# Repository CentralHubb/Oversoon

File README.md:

# Oversoon
Custom PCB design for geolocation sensing, wifi communications, and LED display

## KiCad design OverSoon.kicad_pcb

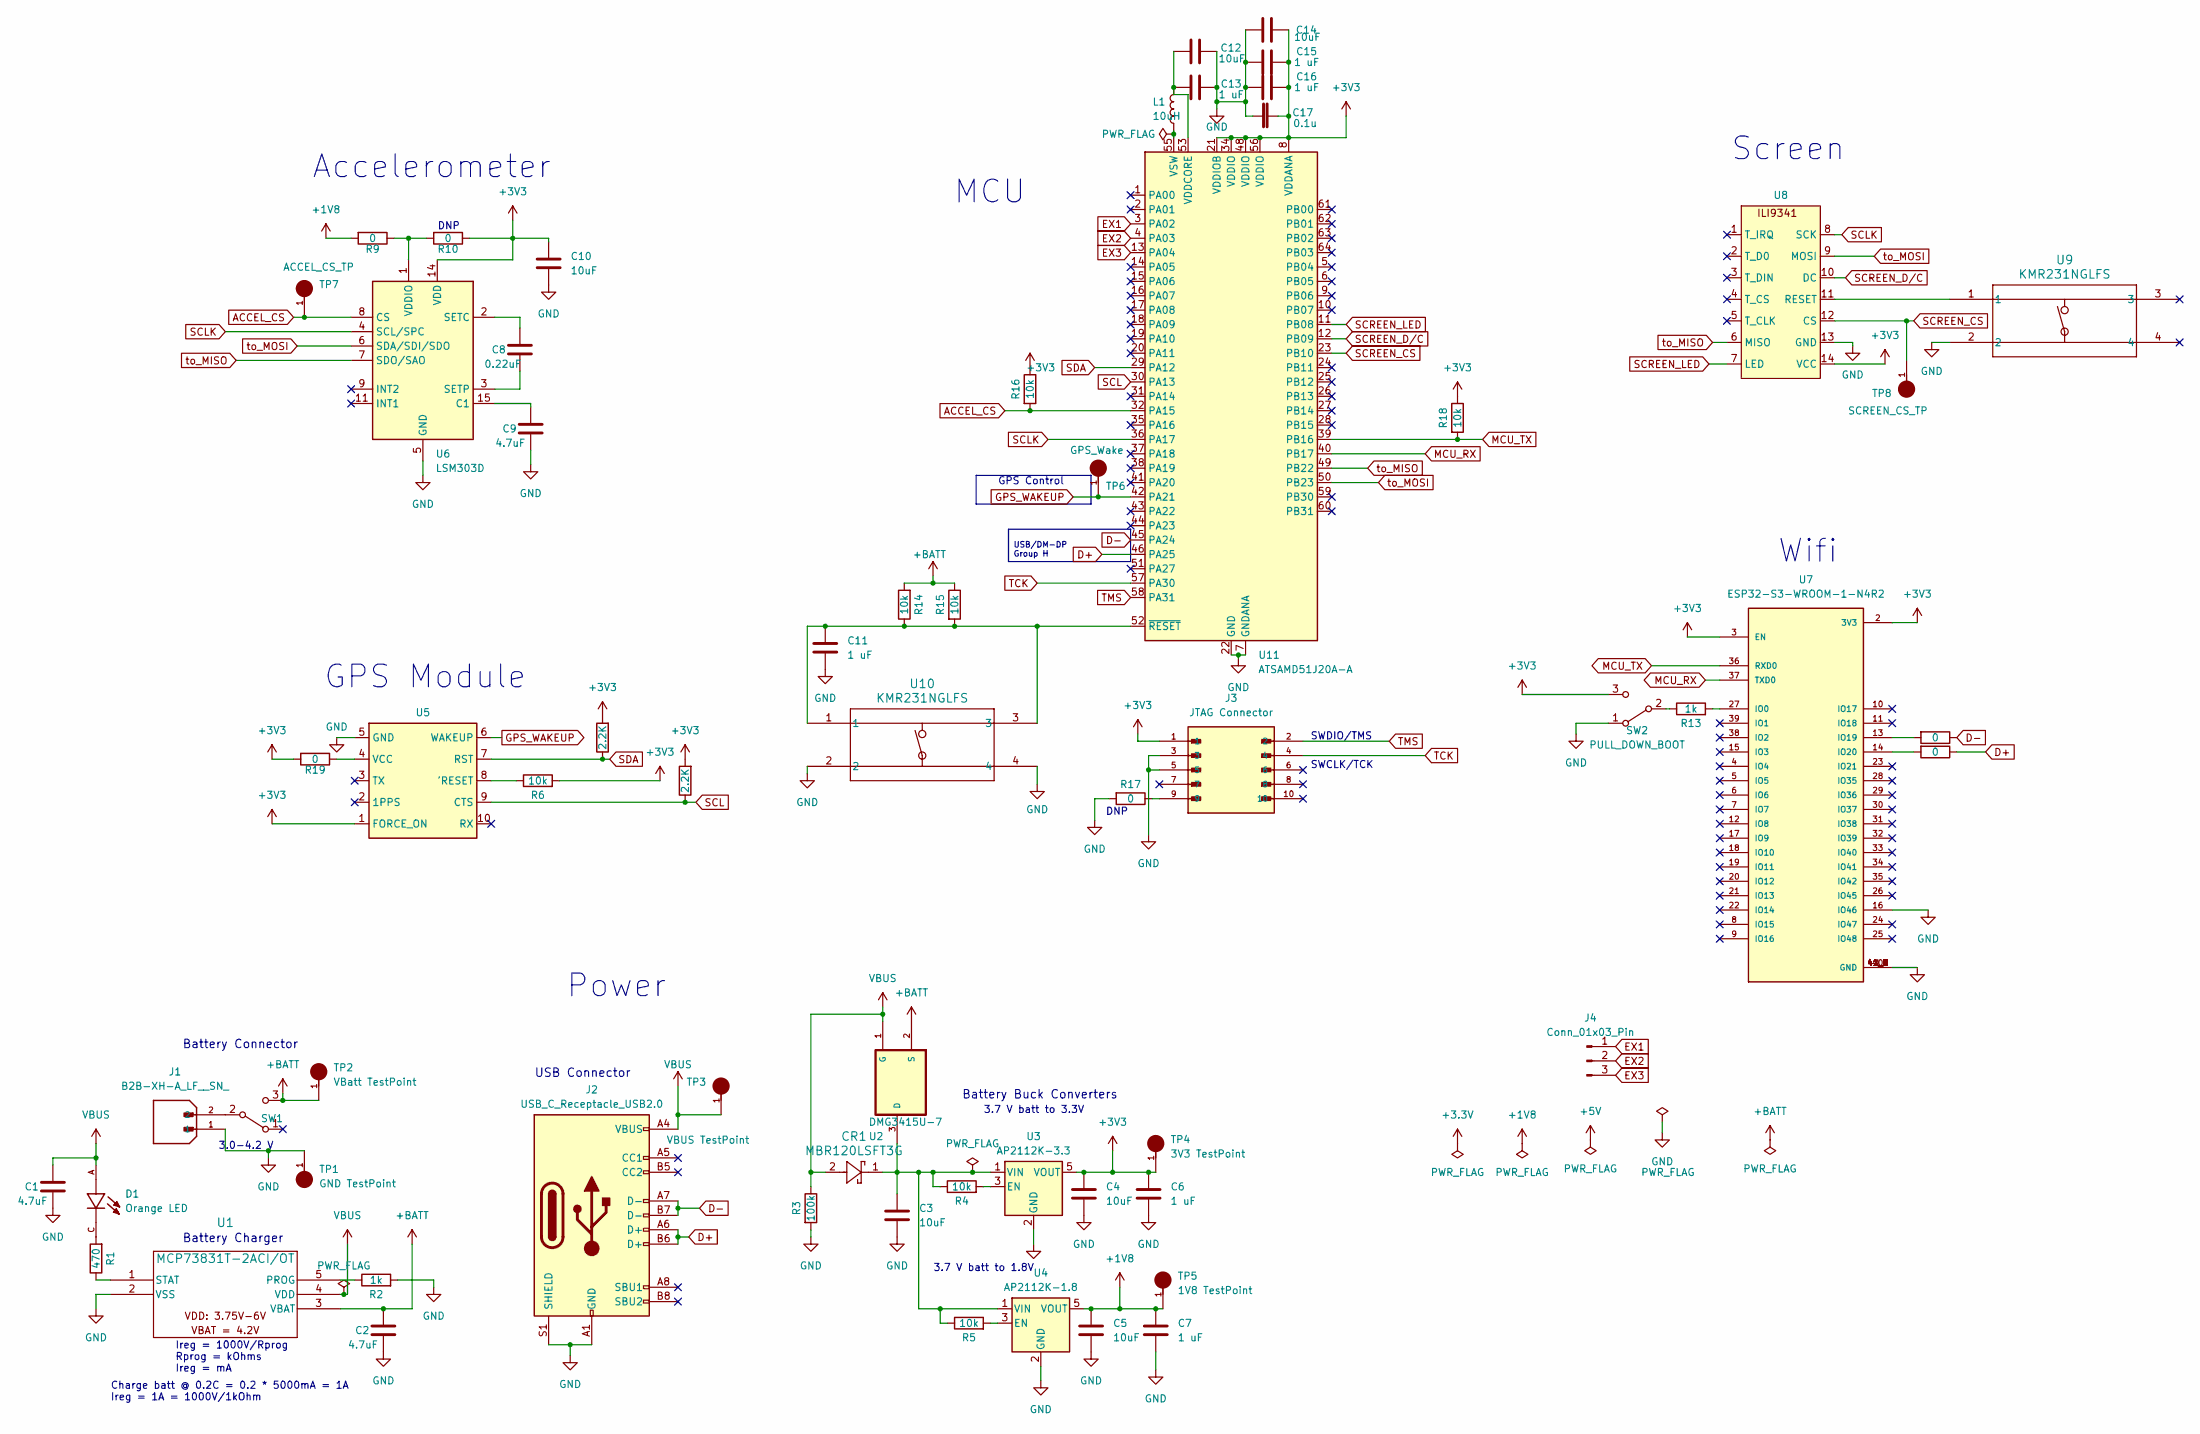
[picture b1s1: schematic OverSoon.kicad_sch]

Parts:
C1, C2, C9: 4.7uF; C_0805_2012Metric_Pad1.18x1.45mm_HandSolder; Mfr P/N GRM21BR71C475KE51L
C3, C4, C5, C10, C12, C14: 10uF; C_0805_2012Metric_Pad1.18x1.45mm_HandSolder; Mfr P/N CC0805JRNPO9BN100
C6, C7, C11, C13, C15, C16: 1 uF; C_0805_2012Metric_Pad1.18x1.45mm_HandSolder; Mfr P/N CL21F105ZBFNNNE
C8: 0.22uF; C_0805_2012Metric_Pad1.18x1.45mm_HandSolder; Mfr P/N GCM21BR71H224KA37L
C17: 0.1u; C_0805_2012Metric_Pad1.18x1.45mm_HandSolder; Mfr P/N 08056D104KAT2A
CR1: MBR120LSFT3G; SDO_SOD-123FL498_OSI; Mfr P/N MBR120LSFT3G
D1: Orange LED; LEDC1608X55N; Mfr P/N LTST-C191KFKT
J1: B2B-XH-A_LF__SN_; JST_B2B-XH-A_LF__SN_; PARTREV N/A
J2: USB_C_Receptacle_USB2.0; USB_C_Receptacle_XKB_U262-16XN-4BVC11; Mfr P/N U262-161N-4BVC11
J3: JTAG Connector; CNC_3221-10-0300-00; Mfr P/N 3221-10-0300-00
J4: Conn_01x03_Pin; PinHeader_1x03_P2.54mm_Vertical; Mfr P/N M20-9990345
L1: 10uH; L_0805_2012Metric_Pad1.15x1.40mm_HandSolder; Mfr P/N LBR2012T100K
R1: 470; R_0805_2012Metric_Pad1.20x1.40mm_HandSolder; Mfr P/N RMCF0805JT470R
R2, R13: 1k; R_0805_2012Metric_Pad1.20x1.40mm_HandSolder; Mfr P/N RMCF0805FT1K00
R3: 100k; R_0805_2012Metric_Pad1.20x1.40mm_HandSolder; Mfr P/N RMCF0805FT100K
R4, R5, R6, R14, R15, R16, R18: 10k; R_0805_2012Metric_Pad1.20x1.40mm_HandSolder; Mfr P/N RMCF0805JT10K0
R7, R8: 2.2K; R_0805_2012Metric_Pad1.20x1.40mm_HandSolder; Mfr P/N RT0805BRD072K23L
R9, R10, R11, R12, R17, R19: 0; R_0805_2012Metric_Pad1.20x1.40mm_HandSolder; Mfr P/N CRCW08050000Z0EAHP
SW1, SW2: PULL_DOWN_BOOT; SW_JS102011SAQN; Mfr P/N JS102011SAQN
TP1: GND TestPoint; HARWIN_S2751-46R; Mfr P/N S2751-46R
TP2: VBatt TestPoint; HARWIN_S2751-46R; Mfr P/N S2751-46R
TP3: VBUS TestPoint; HARWIN_S2751-46R; Mfr P/N S2751-46R
TP4: 3V3 TestPoint; HARWIN_S2751-46R; Mfr P/N S2751-46R
TP5: 1V8 TestPoint; HARWIN_S2751-46R; Mfr P/N S2751-46R
TP6: GPS_Wake; HARWIN_S2751-46R; Mfr P/N S2751-46R
TP7: ACCEL_CS_TP; HARWIN_S2751-46R; Mfr P/N S2751-46R
TP8: SCREEN_CS_TP; HARWIN_S2751-46R; Mfr P/N S2751-46R
U1: MCP73831T-2ACI/OT; SOT-23-5_MC_MCH; Mfr P/N MCP73831T-2ACI/OT
U2: DMG3415U-7; SOT95P240X105-3N; Mfr P/N DMG3415U-7
U3: AP2112K-3.3; SOT-23-5; Mfr P/N AP2112K-3.3TRG1
U4: AP2112K-1.8; SOT-23-5; Mfr P/N AP2112K-1.8TRG1
U5: ORG1510-R02
U6: LSM303D; LGA-16_3x3mm_P0.5mm; Mfr P/N LSM303D
U7: ESP32-S3-WROOM-1-N4R2; XCVR_ESP32-S3-WROOM-1-N4R2; Mfr P/N ESP32-S3-WROOM-1-N4R2
U8: ILI9341; Mfr P/N 6-104910-3
U9, U10: KMR231NGLFS; IC4_KMR231NGLFS_CNK; Mfr P/N KMR231NG LFS
U11: ATSAMD51J20A-A; TQFP-64_10x10mm_P0.5mm; Mfr P/N ATSAMD51J20A-AU

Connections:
+1V8: C5.1, C7.1, R9.2, TP5.1, U4.5 (VOUT)
+3V3: C4.1, C6.1, C10.1, C14.2, C15.2, C16.2, C17.2, J3.1, R6.2, R7.2, R8.2, R10.1, R16.1, R18.1, R19.2, SW2.3 (C), TP4.1, U3.5 (VOUT), U5.1 (FORCE_ON), U6.14 (VDD), U7.2 (3V3), U7.3 (EN), U8.14 (VCC), U11.8 (VDDANA), U11.21 (VDDIOB), U11.34 (VDDIO), U11.48 (VDDIO), U11.56 (VDDIO)
+BATT: C2.1, R14.2, R15.1, SW1.3 (C), TP2.1, U1.3 (VBAT), U2.2 (S)
ACCEL_CS: R16.2, TP7.1, U6.8 (CS), U11.32 (PA15)
D+: J2.A6 (D+), J2.B6 (D+), R12.1, U11.46 (PA25)
D-: J2.A7 (D-), J2.B7 (D-), R11.1, U11.45 (PA24)
EX1: J4.1, U11.3 (PA02)
EX2: J4.2, U11.4 (PA03)
EX3: J4.3, U11.13 (PA04)
GND: C1.2, C2.2, C3.2, C4.2, C5.2, C6.2, C7.2, C9.2, C10.2, C11.2, C12.2, C13.2, C14.1, C15.1, C16.1, C17.1, J1.1, J2.A1 (GND), J2.A12 (GND), J2.B1 (GND), J2.B12 (GND), J2.S1 (SHIELD), J3.3, J3.5, R2.2, R3.2, R17.2, SW2.1 (A), TP1.1, U1.2 (VSS), U3.2 (GND), U4.2 (GND), U5.5 (GND), U6.5 (GND), U6.10 (GND), U6.12 (GND), U6.13 (GND), U6.16 (GND), U7.1 (GND), U7.16 (IO46), U7.40 (GND), U7.41_1 (GND), U7.41_2 (GND), U7.41_3 (GND), U7.41_4 (GND), U7.41_5 (GND), U7.41_6 (GND), U7.41_7 (GND), U7.41_8 (GND), U7.41_9 (GND), U8.13 (GND), U9.2, U10.2, U10.4, U11.7 (GNDANA), U11.22 (GND), U11.33 (GND), U11.47 (GND), U11.54 (GND)
GPS_WAKEUP: TP6.1, U5.6 (WAKEUP), U11.42 (PA21)
MCU_RX: U7.37 (TXD0), U11.40 (PB17)
MCU_TX: R18.2, U7.36 (RXD0), U11.39 (PB16)
unnamed: D1.C, R1.2
unnamed: J3.9, R17.1
unnamed: J1.2, SW1.2 (B)
unnamed: R13.1, SW2.2 (B)
unnamed: R2.1, U1.5 (PROG)
unnamed: R1.1, U1.1 (STAT)
unnamed: C3.1, CR1.1, R4.1, R5.1, U2.3 (D), U3.1 (VIN), U4.1 (VIN)
unnamed: R4.2, U3.3 (EN)
unnamed: R5.2, U4.3 (EN)
unnamed: R6.1, U5.8 ('RESET)
unnamed: R19.1, U5.4 (VCC)
unnamed: C9.1, U6.15 (C1)
unnamed: C8.1, U6.2 (SETC)
unnamed: C8.2, U6.3 (SETP)
unnamed: R9.1, R10.2, U6.1 (VDDIO)
unnamed: R13.2, U7.27 (IO0)
unnamed: R11.2, U7.13 (IO19)
unnamed: R12.2, U7.14 (IO20)
unnamed: U8.11 (RESET), U9.1
unnamed: C12.1, C13.1, L1.2, U11.53 (VDDCORE)
unnamed: L1.1, U11.55 (VSW)
unnamed: C11.1, R14.1, R15.2, U10.1, U10.3, U11.52 (~RESET)
SCL: R8.1, U5.9 (CTS), U11.30 (PA13)
SCLK: U6.4 (SCL/SPC), U8.8 (SCK), U11.36 (PA17)
SCREEN_CS: TP8.1, U8.12 (CS), U11.23 (PB10)
SCREEN_D/C: U8.10 (DC), U11.12 (PB09)
SCREEN_LED: U8.7 (LED), U11.11 (PB08)
SDA: R7.1, U5.7 (RST), U11.29 (PA12)
TCK: J3.4, U11.57 (PA30)
TMS: J3.2, U11.58 (PA31)
VBUS: C1.1, CR1.2, D1.A, J2.A4 (VBUS), J2.A9 (VBUS), J2.B4 (VBUS), J2.B9 (VBUS), R3.1, TP3.1, U1.4 (VDD), U2.1 (G)
to_MISO: U6.7 (SDO/SAO), U8.6 (MISO), U11.49 (PB22)
to_MOSI: U6.6 (SDA/SDI/SDO), U8.9 (MOSI), U11.50 (PB23)

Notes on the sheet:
USB/DM-DP Group H
Wifi
GPS Control
Power
Accelerometer
DNP
SWCLK/TCK
3.7 V batt to 1.8V
3.0-4.2 V
Screen
USB Connector
Battery Charger
Ireg = 1000V/Rprog Rprog = kOhms Ireg = mA
Battery Buck Converters
Battery Connector
MCU
Charge batt @ 0.2C = 0.2 * 5000mA = 1A Ireg = 1A = 1000V/1kOhm
SWDIO/TMS
3.7 V batt to 3.3V
GPS Module

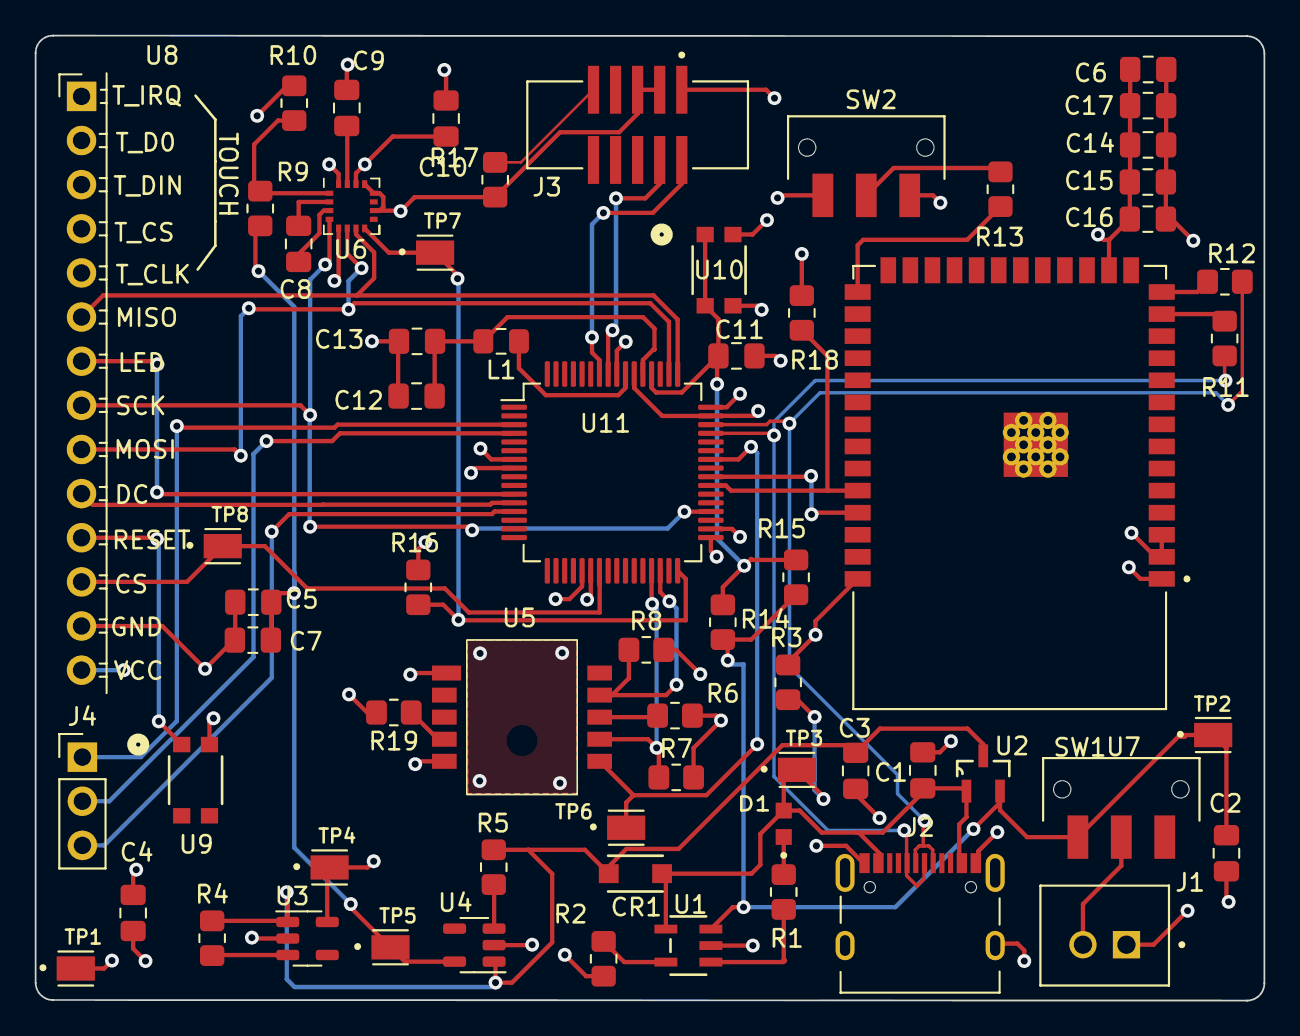
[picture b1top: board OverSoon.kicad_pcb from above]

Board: 4 copper layers, 70.7 x 55.5 mm, 64 parts (0 on the bottom side), 46 nets.

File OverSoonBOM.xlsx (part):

Source: | C:\Users\theol\OneDrive\Documents\KiCad\7.0\projects\OverSoon\OverSoon.kicad_sch
Date: | 45556
Tool: | Eeschema 7.0.8
Generator: | D:\Program Files\KiCad\7.0\bin\scripting\plugins/bom_csv_grouped_by_value.py
Component Count: | 125
Collated Components:
Item | Qty | Reference(s) | Value | LibPart | Footprint | Datasheet | Description | Mfr | Mfr P/N | Supplier 1 | Supplier 1 P/N
1 | 7 | C1, C2, C9 | 4.7uF | Device:C | Capacitor_SMD:C_0805_2012Metric_Pad1.18x1.45mm_HandSolder | https://search.murata.co.jp/Ceramy/image/img/A01X/G101/ENG/G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 | CAP CER 4.7UF 16V X7R 0805 | Murata Electronics | GRM21BR71C475KE51L | Digikey | 490-14466-2-ND
2 | 13 | C3, C4, C5, C10, C12, C14 | 10uF | Device:C | Capacitor_SMD:C_0805_2012Metric_Pad1.18x1.45mm_HandSolder | https://www.yageo.com/upload/media/product/productsearch/dat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 | CAP CER 10PF 50V C0G/NPO 0805 | YAGEO | CC0805JRNPO9BN100 | Digikey | 311-1099-2-ND
3 | 13 | C6, C7, C11, C13, C15, C16 | 1 uF | Device:C | Capacitor_SMD:C_0805_2012Metric_Pad1.18x1.45mm_HandSolder | https://www.samsungsem.com/kr/support/product-search/mlcc/CL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 | CAP CER 1UF 50V Y5V 0805 | Samsung Electro-Mechanics | CL21F105ZBFNNNE | Digikey | 1276-3010-2-ND
4 | 3 | C8 | 0.22uF | Device:C | Capacitor_SMD:C_0805_2012Metric_Pad1.18x1.45mm_HandSolder | https://search.murata.co.jp/Ceramy/image/img/A01X/G101/ENG/G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 | CAP CER 0.22UF 50V X7R 0805 | Murata Electronics | GCM21BR71H224KA37L | Digikey | 490-4970-2-ND
5 | 3 | C17 | 0.1u | :C_1 | Capacitor_SMD:C_0805_2012Metric_Pad1.18x1.45mm_HandSolder | https://datasheets.kyocera-avx.com/cx5r.pdf | CAP CER 0.1UF 6.3V X5R 0805 | KYOCERA AVX | 08056D104KAT2A | Digikey | 478-08056D104KAT2ATR-ND
6 | 3 | CR1 | MBR120LSFT3G | RAIN_X symbols lib:MBR120LSFT3G | RAIN_X footprints lib:SDO_SOD-123FL498_OSI | https://www.onsemi.com/pdf/datasheet/mbr120lsft1-d.pdf | DIODE SCHOTTKY 20V 1A SOD123FL | onsemi | MBR120LSFT3G | Digikey | MBR120LSFT3GOSTR-ND
7 | 3 | D1 | Orange LED | RAIN_X symbols lib:LTST-C191KFKT | RAIN_X footprints lib:LEDC1608X55N | https://optoelectronics.liteon.com/upload/download/DS22-2000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 | LED ORANGE CLEAR SMD | Lite-On Inc. | LTST-C191KFKT | Digikey | 160-1445-2-ND
8 | 1 | J1 | B2B-XH-A_LF__SN_ | RAIN_X symbols lib:B2B-XH-A_LF__SN_ | RAIN_X footprints lib:JST_B2B-XH-A_LF__SN_ | https://www.jst-mfg.com/product/pdf/eng/eXH.pdf | Connector Header Through Hole 2 position 0.098 (2.50mm) | JST Sales America Inc. | B2B-XH-AM | Digikey | 455-B2B-XH-AM-ND
9 | 2 | J2 | USB_C_Receptacle_USB2.0 | Connector:USB_C_Receptacle_USB2.0 | Connector_USB:USB_C_Receptacle_XKB_U262-16XN-4BVC11 | https://datasheet.lcsc.com/lcsc/2110151630_XKB-Connectivity-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 | 3A USB 3.1 1 260â„ƒ Surface Mount 16P Female -40â„ƒ~+85â„ƒ Gold Copper Alloy Ty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 | XKB Connectivity | U262-161N-4BVC11 | LCSC.com | C319148
10 | 1 | J3 | JTAG Connector | RAIN_X symbols lib:3221-10-0300-00 | RAIN_X footprints lib:CNC_3221-10-0300-00 | http://www.cnctech.us/pdfs/3221-XX-0300-00_.pdf | Connector Header Surface Mount 10 position 0.050 (1.27mm) | CNC Tech | 3221-10-0300-00 | Digikey | 1175-1735-ND
11 | 2 | J4 | Conn_01x03_Pin | Connector:Conn_01x03_Pin | Connector_PinHeader_2.54mm:PinHeader_1x03_P2.54mm_Vertical | https://cdn.harwin.com/pdfs/M20-999.pdf | CONN HEADER VERT 3POS 2.54MM | Harwin Inc. | M20-9990345 | Digkey | 952-2263-ND
12 | 3 | L1 | 10uH | Device:L | Inductor_SMD:L_0805_2012Metric_Pad1.15x1.40mm_HandSolder | https://mm.digikey.com/Volume0/opasdata/d220001/medias/docus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 | FIXED IND 10UH 150MA 360MOHM SMD | Taiyo Yuden | LBR2012T100K | Digikey | 587-2045-2-ND
13 | 3 | R1 | 470 | Device:R | Resistor_SMD:R_0805_2012Metric_Pad1.20x1.40mm_HandSolder | https://www.seielect.com/catalog/sei-rmcf_rmcp.pdf | RES 470 OHM 5% 1/8W 0805 | Stackpole Electronics Inc | RMCF0805JT470R | Digikey | RMCF0805JT470RTR-ND
14 | 5 | R2, R13 | 1k | Device:R | Resistor_SMD:R_0805_2012Metric_Pad1.20x1.40mm_HandSolder | https://www.seielect.com/catalog/sei-rmcf_rmcp.pdf | RES 1K OHM 1% 1/8W 0805 | Stackpole Electronics Inc | RMCF0805FT1K00 | Digikey | RMCF0805FT1K00TR-ND
15 | 3 | R3 | 100k | Device:R | Resistor_SMD:R_0805_2012Metric_Pad1.20x1.40mm_HandSolder | https://www.seielect.com/catalog/sei-rmcf_rmcp.pdf | RES 100K OHM 1% 1/8W 0805 | Stackpole Electronics Inc | RMCF0805FT100K | Digikey | RMCF0805FT100KTR-ND
16 | 12 | R4, R5, R6, R14, R15, R16, R18 | 10k | Device:R | Resistor_SMD:R_0805_2012Metric_Pad1.20x1.40mm_HandSolder | https://www.seielect.com/catalog/sei-rmcf_rmcp.pdf | RES 10K OHM 5% 1/8W 0805 | Stackpole Electronics Inc | RMCF0805JT10K0 | Digikey | RMCF0805JT10K0TR-ND
17 | 5 | R7, R8 | 2.2K | Device:R | Resistor_SMD:R_0805_2012Metric_Pad1.20x1.40mm_HandSolder | https://www.yageo.com/upload/media/product/app/datasheet/rch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 | RES 2.23K OHM 0.1% 1/8W 0805 | YAGEO | RT0805BRD072K23L | Digikey | 13-RT0805BRD072K23LTR-ND
18 | 12 | R9, R10, R11, R12, R17, R19 | 0 | Device:R | Resistor_SMD:R_0805_2012Metric_Pad1.20x1.40mm_HandSolder | https://www.vishay.com/docs/20043/crcwhpe3.pdf | RES SMD 0 OHM JUMPER 1/2W 0805 | Vishay Dale | CRCW08050000Z0EAHP | Digikey | 541-0.0TBTR-ND
19 | 4 | SW1, SW2 | PULL_DOWN_BOOT | Switch:SW_SPDT | RAIN_X footprints lib:SW_JS102011SAQN | https://www.ckswitches.com/media/1422/js.pdf | SWITCH SLIDE SPDT 300MA 6V | C&K | JS102011SAQN | DigiKey | 401-1999-2-ND
20 | 1 | TP1 | GND TestPoint | RAIN_X symbols lib:S2751-46R | RAIN_X footprints lib:HARWIN_S2751-46R | https://cdn.harwin.com/pdfs/S2751R.pdf | PC TEST POINT NATURAL | Harwin | S2751-46R | Digikey | 952-2664-2-ND
21 | 1 | TP2 | VBatt TestPoint | RAIN_X symbols lib:S2751-46R | RAIN_X footprints lib:HARWIN_S2751-46R | https://cdn.harwin.com/pdfs/S2751R.pdf | PC TEST POINT NATURAL | Harwin | S2751-46R | Digikey | 952-2664-2-ND
22 | 1 | TP3 | VBUS TestPoint | RAIN_X symbols lib:S2751-46R | RAIN_X footprints lib:HARWIN_S2751-46R | https://cdn.harwin.com/pdfs/S2751R.pdf | PC TEST POINT NATURAL | Harwin | S2751-46R | Digikey | 952-2664-2-ND
23 | 1 | TP4 | 3V3 TestPoint | RAIN_X symbols lib:S2751-46R | RAIN_X footprints lib:HARWIN_S2751-46R | https://cdn.harwin.com/pdfs/S2751R.pdf | PC TEST POINT NATURAL | Harwin | S2751-46R | Digikey | 952-2664-2-ND
24 | 1 | TP5 | 1V8 TestPoint | RAIN_X symbols lib:S2751-46R | RAIN_X footprints lib:HARWIN_S2751-46R | https://cdn.harwin.com/pdfs/S2751R.pdf | PC TEST POINT NATURAL | Harwin | S2751-46R | Digikey | 952-2664-2-ND
25 | 1 | TP6 | GPS_Wake | RAIN_X symbols lib:S2751-46R | RAIN_X footprints lib:HARWIN_S2751-46R | https://cdn.harwin.com/pdfs/S2751R.pdf | PC TEST POINT NATURAL | Harwin | S2751-46R | Digikey | 952-2664-2-ND
26 | 1 | TP7 | ACCEL_CS_TP | RAIN_X symbols lib:S2751-46R | RAIN_X footprints lib:HARWIN_S2751-46R | https://cdn.harwin.com/pdfs/S2751R.pdf | PC TEST POINT NATURAL | Harwin | S2751-46R | Digikey | 952-2664-2-ND
27 | 1 | TP8 | SCREEN_CS_TP | RAIN_X symbols lib:S2751-46R | RAIN_X footprints lib:HARWIN_S2751-46R | https://cdn.harwin.com/pdfs/S2751R.pdf | PC TEST POINT NATURAL | Harwin | S2751-46R | Digikey | 952-2664-2-ND
28 | 2 | U1 | MCP73831T-2ACI/OT | RAIN_X symbols lib:MCP73831T-2ACI_OT | RAIN_X footprints lib:SOT-23-5_MC_MCH | https://ww1.microchip.com/downloads/en/DeviceDoc/MCP73831-Fa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 | IC BATT CNTL LI-ION 1CEL SOT23-5 | Microchip Technology | MCP73831T-2ACI/OT | Digikey | MCP73831T-2ACI/OTTR-ND
29 | 2 | U2 | DMG3415U-7 | RAIN_X symbols lib:DMG3415U-7 | RAIN_X footprints lib:SOT95P240X105-3N | https://mm.digikey.com/Volume0/opasdata/d220001/medias/docus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 | MOSFET P-CH 20V 4A SOT23-3 | Diodes Incorporated | DMG3415U-7 | Digikey | DMG3415UDITR-ND
30 | 2 | U3 | AP2112K-3.3 | Regulator_Linear:AP2112K-3.3 | Package_TO_SOT_SMD:SOT-23-5 | https://www.diodes.com/assets/Datasheets/AP2112.pdf | IC REG LINEAR 3.3V 600MA SOT25 | Diodes Incorporated | AP2112K-3.3TRG1 | Digikey | AP2112K-3.3TRG1DITR-ND
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
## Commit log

2024-12-24 Uploading KiCAD files
